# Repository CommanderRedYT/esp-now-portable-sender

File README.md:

# esp-now-portable-sender
A small PCB with a ESP-32 and a button cell to send ESP-Now messages

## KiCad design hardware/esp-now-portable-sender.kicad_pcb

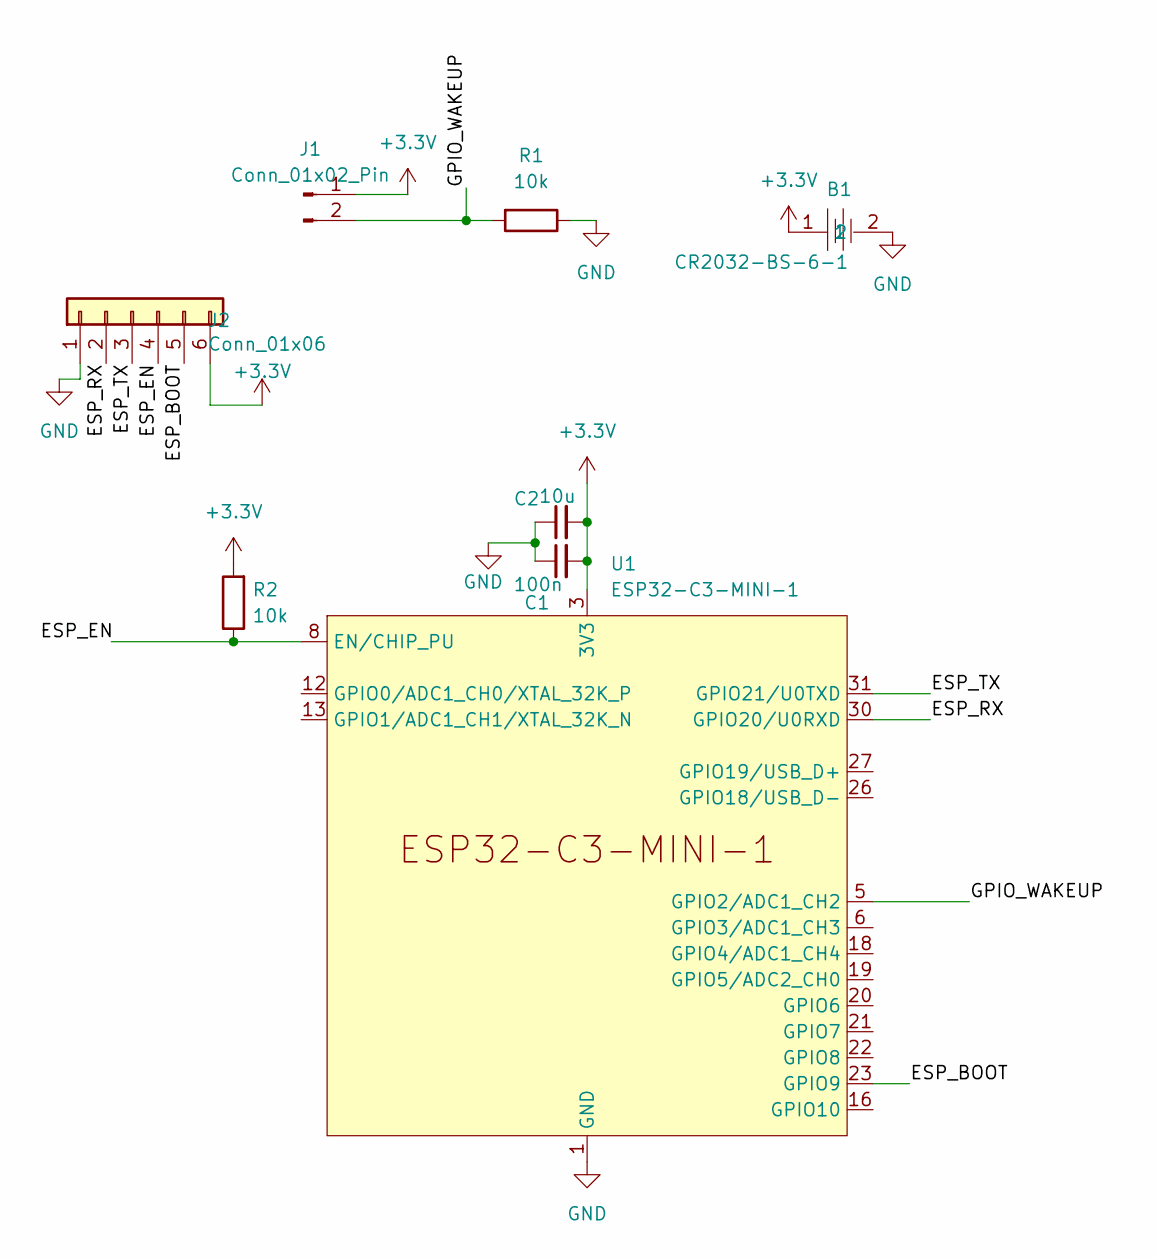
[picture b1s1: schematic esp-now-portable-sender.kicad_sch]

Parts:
B1: CR2032-BS-6-1; BAT-TH_CR2032-BS-6-1; LCSC Part C70377
C1: 100n; C_0402_1005Metric; LCSC Part C1525
C2: 10u; C_0603_1608Metric; LCSC Part C19702
J1: Conn_01x02_Pin; PinHeader_1x02_P2.54mm_Vertical; LCSC Part DNP
J2: Conn_01x06; PinHeader_1x06_P2.54mm_Vertical; LCSC Part DNP
R1, R2: 10k; R_0402_1005Metric; LCSC Part C25744
U1: ESP32-C3-MINI-1; LCSC Part C2838502

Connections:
+3.3V: B1.1, C1.2, C2.2, J1.1, J2.6, R2.2, U1.3 (3V3)
/ESP_BOOT: J2.5, U1.23 (GPIO9)
/ESP_EN: J2.4, R2.1, U1.8 (EN/CHIP_PU)
/ESP_RX: J2.2, U1.30 (GPIO20/U0RXD)
/ESP_TX: J2.3, U1.31 (GPIO21/U0TXD)
/GPIO_WAKEUP: J1.2, R1.2, U1.5 (GPIO2/ADC1_CH2)
GND: B1.2, C1.1, C2.1, J2.1, R1.1, U1.1 (GND), U1.2 (GND), U1.11 (GND), U1.14 (GND), U1.36 (GND), U1.37 (GND), U1.38 (GND), U1.39 (GND), U1.40 (GND), U1.41 (GND), U1.42 (GND), U1.43 (GND), U1.44 (GND), U1.45 (GND), U1.46 (GND), U1.47 (GND), U1.48 (GND), U1.49 (GND), U1.50 (GND), U1.51 (GND), U1.52 (GND), U1.53 (GND)

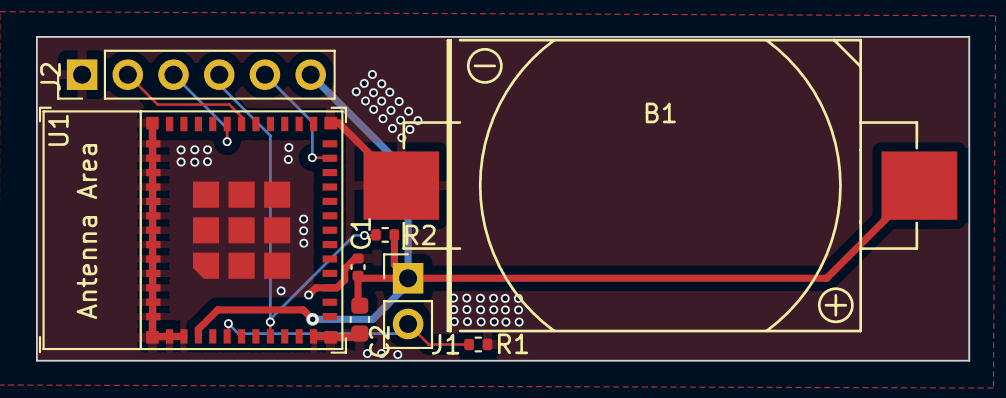
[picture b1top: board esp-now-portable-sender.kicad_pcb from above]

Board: 2 copper layers, 51.8 x 18.0 mm, 8 parts (0 on the bottom side), 7 nets.

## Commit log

2023-12-03 Implemented firmware
